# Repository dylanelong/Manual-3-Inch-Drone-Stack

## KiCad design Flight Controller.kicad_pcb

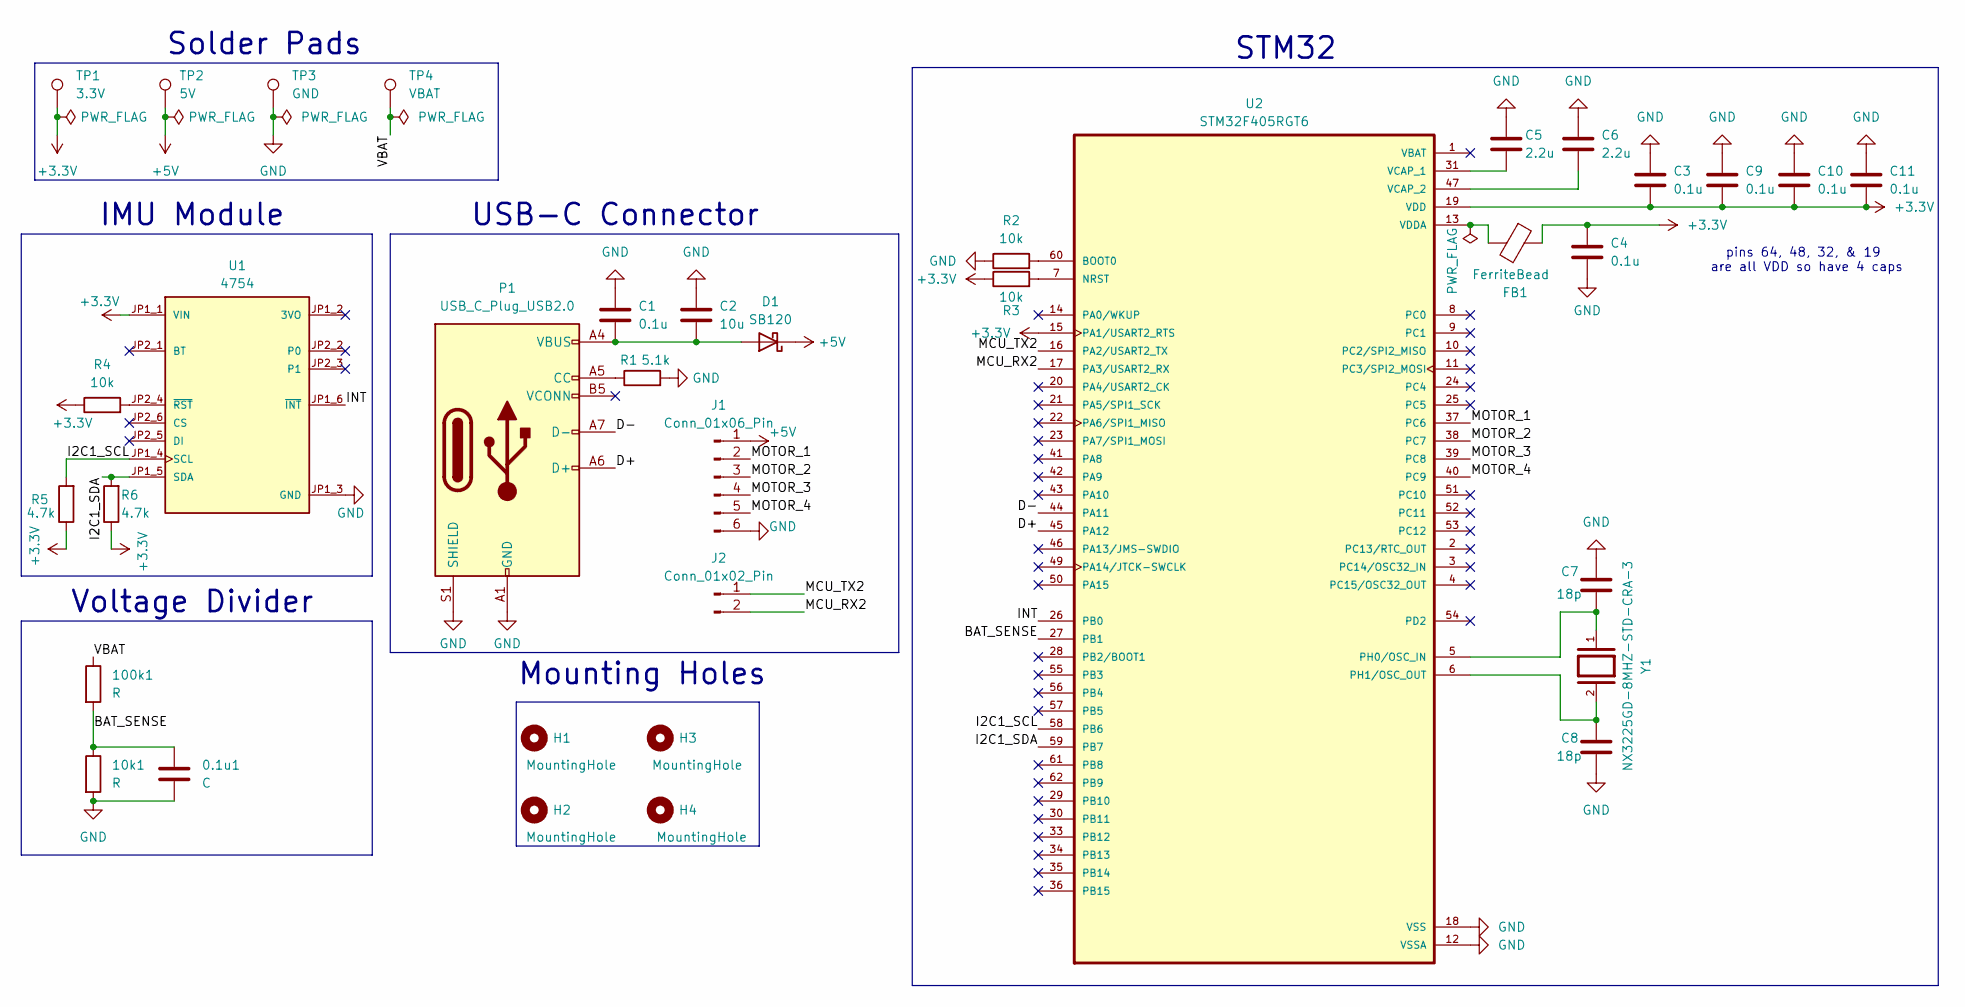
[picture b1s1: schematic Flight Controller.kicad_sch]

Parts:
0.1u1: C; C_0805_2012Metric_Pad1.18x1.45mm_HandSolder
10k1, 100k1: R; R_0805_2012Metric
C1, C3, C4, C9, C10, C11: 0.1u; C_0805_2012Metric_Pad1.18x1.45mm_HandSolder
C2: 10u; C_0805_2012Metric_Pad1.18x1.45mm_HandSolder
C5, C6: 2.2u; C_0805_2012Metric_Pad1.18x1.45mm_HandSolder
C7, C8: 18p; C_0805_2012Metric_Pad1.18x1.45mm_HandSolder
D1: SB120; D_0603_1608Metric
FB1: FerriteBead; BEADC1608X95N
H1, H2, H3, H4: MountingHole; MountingHole_3.2mm_M3
J1: Conn_01x06_Pin; PinHeader_1x06_P2.54mm_Vertical
J2: Conn_01x02_Pin; PinHeader_1x02_P2.00mm_Vertical_SMD_Pin1Right
P1: USB_C_Plug_USB2.0; USB_C_Receptacle_GCT_USB4105-xx-A_16P_TopMnt_Horizontal
R1: 5.1k; R_0805_2012Metric
R2, R3, R4: 10k; R_0805_2012Metric
R5, R6: 4.7k; R_0805_2012Metric
TP1: 3.3V; TestPoint_Pad_D3.0mm
TP2: 5V; TestPoint_Pad_D3.0mm
TP3: GND; TestPoint_Pad_D3.0mm
TP4: VBAT; TestPoint_Pad_D3.0mm
U1: 4754; BNO085 Mount; PARTREV 2021-03-16
U2: STM32F405RGT6; LQFP-64_10x10mm_P0.5mm; PARTREV LTR
Y1: NX3225GD-8MHZ-STD-CRA-3; XTAL_NX3225GD-8MHZ-STD-CRA-3

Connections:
+3.3V: C3.2, C4.2, C9.2, C10.2, C11.2, FB1.1, R3.1, R4.1, R5.1, R6.1, TP1.1, U1.JP1_1 (VIN), U2.15 (PA1/USART2_RTS), U2.19 (VDD), U2.32 (VDD), U2.48 (VDD), U2.64 (VDD)
+5V: D1.1 (K), J1.1, TP2.1
/BAT_SENSE: 0.1u1.1, 10k1.1, 100k1.2, U2.27 (PB1)
/D+: P1.A6 (D+), U2.45 (PA12)
/D-: P1.A7 (D-), U2.44 (PA11)
/I2C1_SCL: R5.2, U1.JP1_4 (SCL), U2.58 (PB6)
/I2C1_SDA: R6.2, U1.JP1_5 (SDA), U2.59 (PB7)
/INT: U1.JP1_6 (~INT), U2.26 (PB0)
/MCU_RX2: J2.2, U2.17 (PA3/USART2_RX)
/MCU_TX2: J2.1, U2.16 (PA2/USART2_TX)
/MOTOR_1: J1.2, U2.37 (PC6)
/MOTOR_2: J1.3, U2.38 (PC7)
/MOTOR_3: J1.4, U2.39 (PC8)
/MOTOR_4: J1.5, U2.40 (PC9)
/VBAT: 100k1.1, TP4.1
GND: 0.1u1.2, 10k1.2, C1.1, C2.1, C3.1, C4.1, C5.1, C6.1, C7.1, C8.1, C9.1, C10.1, C11.1, J1.6, P1.A1 (GND), P1.A12 (GND), P1.B1 (GND), P1.B12 (GND), P1.S1 (SHIELD), R1.2, R2.1, TP3.1, U1.JP1_3 (GND), U2.12 (VSSA), U2.18 (VSS), U2.63 (VSS)
unnamed: C1.2, C2.2, D1.2 (A), P1.A4 (VBUS), P1.A9 (VBUS), P1.B4 (VBUS), P1.B9 (VBUS)
unnamed: P1.A5 (CC), R1.1
unnamed: R4.2, U1.JP2_4 (~RST)
unnamed: R2.2, U2.60 (BOOT0)
unnamed: R3.2, U2.7 (NRST)
unnamed: C7.2, U2.5 (PH0/OSC_IN), Y1.1
unnamed: C8.2, U2.6 (PH1/OSC_OUT), Y1.2
unnamed: C5.2, U2.31 (VCAP_1)
unnamed: C6.2, U2.47 (VCAP_2)
unnamed: FB1.2, U2.13 (VDDA)

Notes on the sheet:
Voltage Divider
pins 64, 48, 32, & 19 are all VDD so have 4 caps
USB-C Connector
Solder Pads
IMU Module
Mounting Holes
STM32

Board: 2 copper layers, 36 parts (6 on the bottom side), 26 nets, no tracks yet.

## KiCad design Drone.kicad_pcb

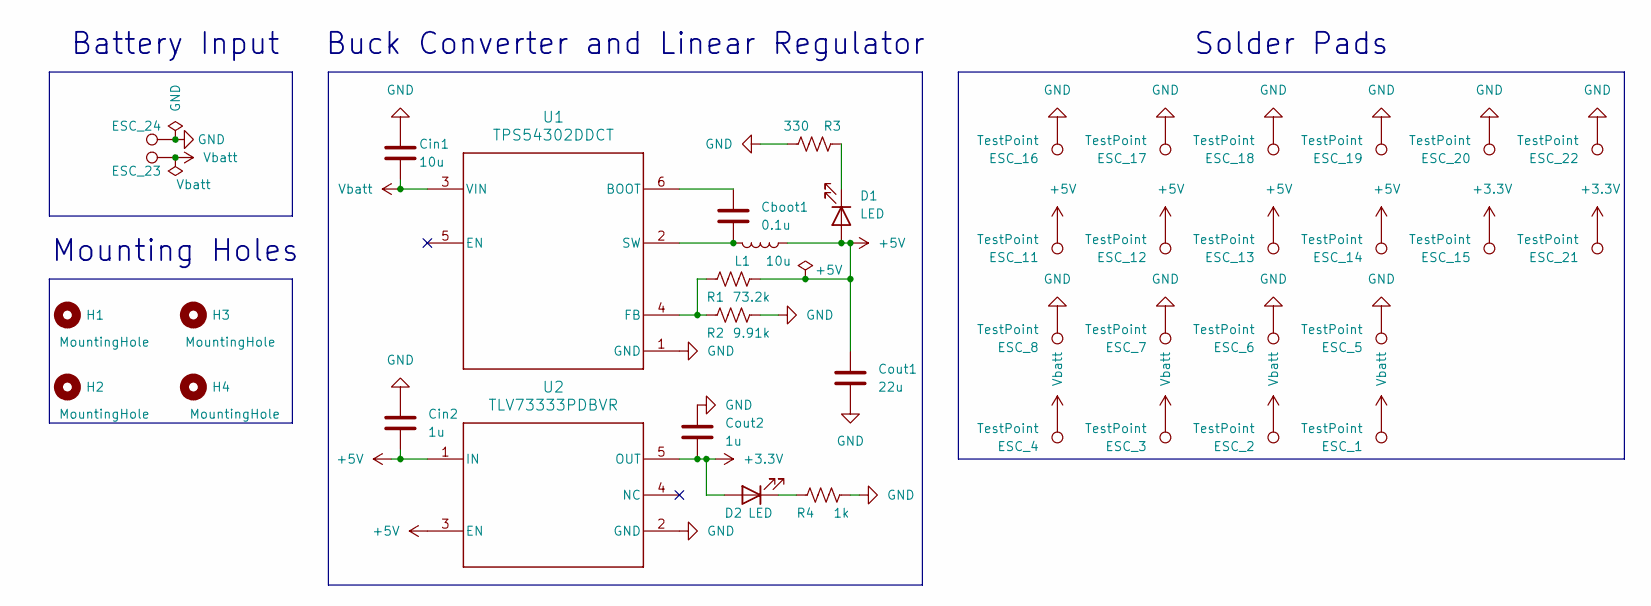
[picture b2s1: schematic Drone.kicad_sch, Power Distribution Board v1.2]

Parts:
Cboot1: 0.1u; C_0805_2012Metric_Pad1.18x1.45mm_HandSolder
Cin1: 10u; C_0805_2012Metric_Pad1.18x1.45mm_HandSolder
Cin2: 1u; C_0805_2012Metric_Pad1.18x1.45mm_HandSolder
Cout1: 22u; C_0805_2012Metric_Pad1.18x1.45mm_HandSolder
Cout2: 1u; C_0805_2012Metric_Pad1.18x1.45mm_HandSolder
D1, D2: LED; LED_0805_2012Metric
ESC_1, ESC_2, ESC_3, ESC_4, ESC_5, ESC_6, ESC_7, ESC_8, ESC_11, ESC_12, ESC_13, ESC_14, ESC_15, ESC_16, ESC_17, ESC_18, ESC_19, ESC_20, ESC_21, ESC_22, ESC_23, ESC_24: TestPoint; TestPoint_Pad_D3.0mm
H1, H2, H3, H4: MountingHole; MountingHole_3.2mm_M3
L1: 10u; L_Bourns_SRN6045TA
R1: 73.2k; R_0805_2012Metric
R2: 9.91k; R_0805_2012Metric
R3: 330; R_0805_2012Metric
R4: 1k; R_0805_2012Metric
U1: TPS54302DDCT; DDC0006A_L
U2: TLV73333PDBVR; DBV0005A_L

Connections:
+3.3V: Cout2.2, D2.2 (A), ESC_15.1, ESC_21.1, U2.5 (OUT)
+5V: Cin2.2, Cout1.1, D1.2 (A), ESC_11.1, ESC_12.1, ESC_13.1, ESC_14.1, L1.1, R1.2, U2.1 (IN), U2.3 (EN)
GND: Cin1.1, Cin2.1, Cout1.2, Cout2.1, ESC_5.1, ESC_6.1, ESC_7.1, ESC_8.1, ESC_16.1, ESC_17.1, ESC_18.1, ESC_19.1, ESC_20.1, ESC_22.1, ESC_24.1, R2.2, R3.2, R4.2, U1.1 (GND), U2.2 (GND); also elsewhere on the board
unnamed: D1.1 (K), R3.1
unnamed: D2.1 (K), R4.1
unnamed: Cboot1.1, U1.6 (BOOT)
unnamed: R1.1, R2.1, U1.4 (FB)
unnamed: Cboot1.2, L1.2, U1.2 (SW)
Vbatt: Cin1.2, ESC_1.1, ESC_2.1, ESC_3.1, ESC_4.1, ESC_23.1, U1.3 (VIN)

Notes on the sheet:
Buck Converter and Linear Regulator
Battery Input
Solder Pads
Mounting Holes

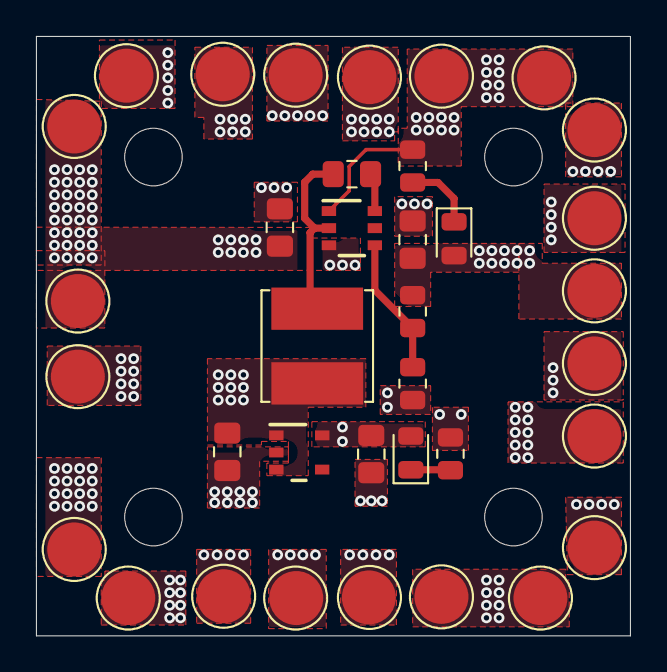
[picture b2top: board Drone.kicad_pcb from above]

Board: 4 copper layers, 33.0 x 33.3 mm, 40 parts (0 on the bottom side), 9 nets.

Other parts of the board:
ESC_10: TestPoint; TestPoint_Pad_D3.0mm

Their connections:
GND: ESC_10.1; also elsewhere on the board
